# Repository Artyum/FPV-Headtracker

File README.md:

## FPH Headtracker for RC Airplanes

The FPH Headtracker is an advanced device designed for RC airplane enthusiasts. It enables pilots to control the camera on their RC aircraft by simply moving their head. This immersive technology enhances the flying experience by providing a first-person view (FPV) that moves naturally with the pilot's head movements. The headtracker system is equipped with sensors that accurately track the pilot's head position and transmit these movements to the camera gimbal on the RC airplane, allowing for precise and intuitive control. This innovation is particularly useful for aerial photography, racing, and immersive flight simulations, making the flying experience more engaging and realistic.

## Demonstration video
[MPX Mentor FPV with HEADTRACKER](https://www.youtube.com/watch?v=0JXXjhNscpw)

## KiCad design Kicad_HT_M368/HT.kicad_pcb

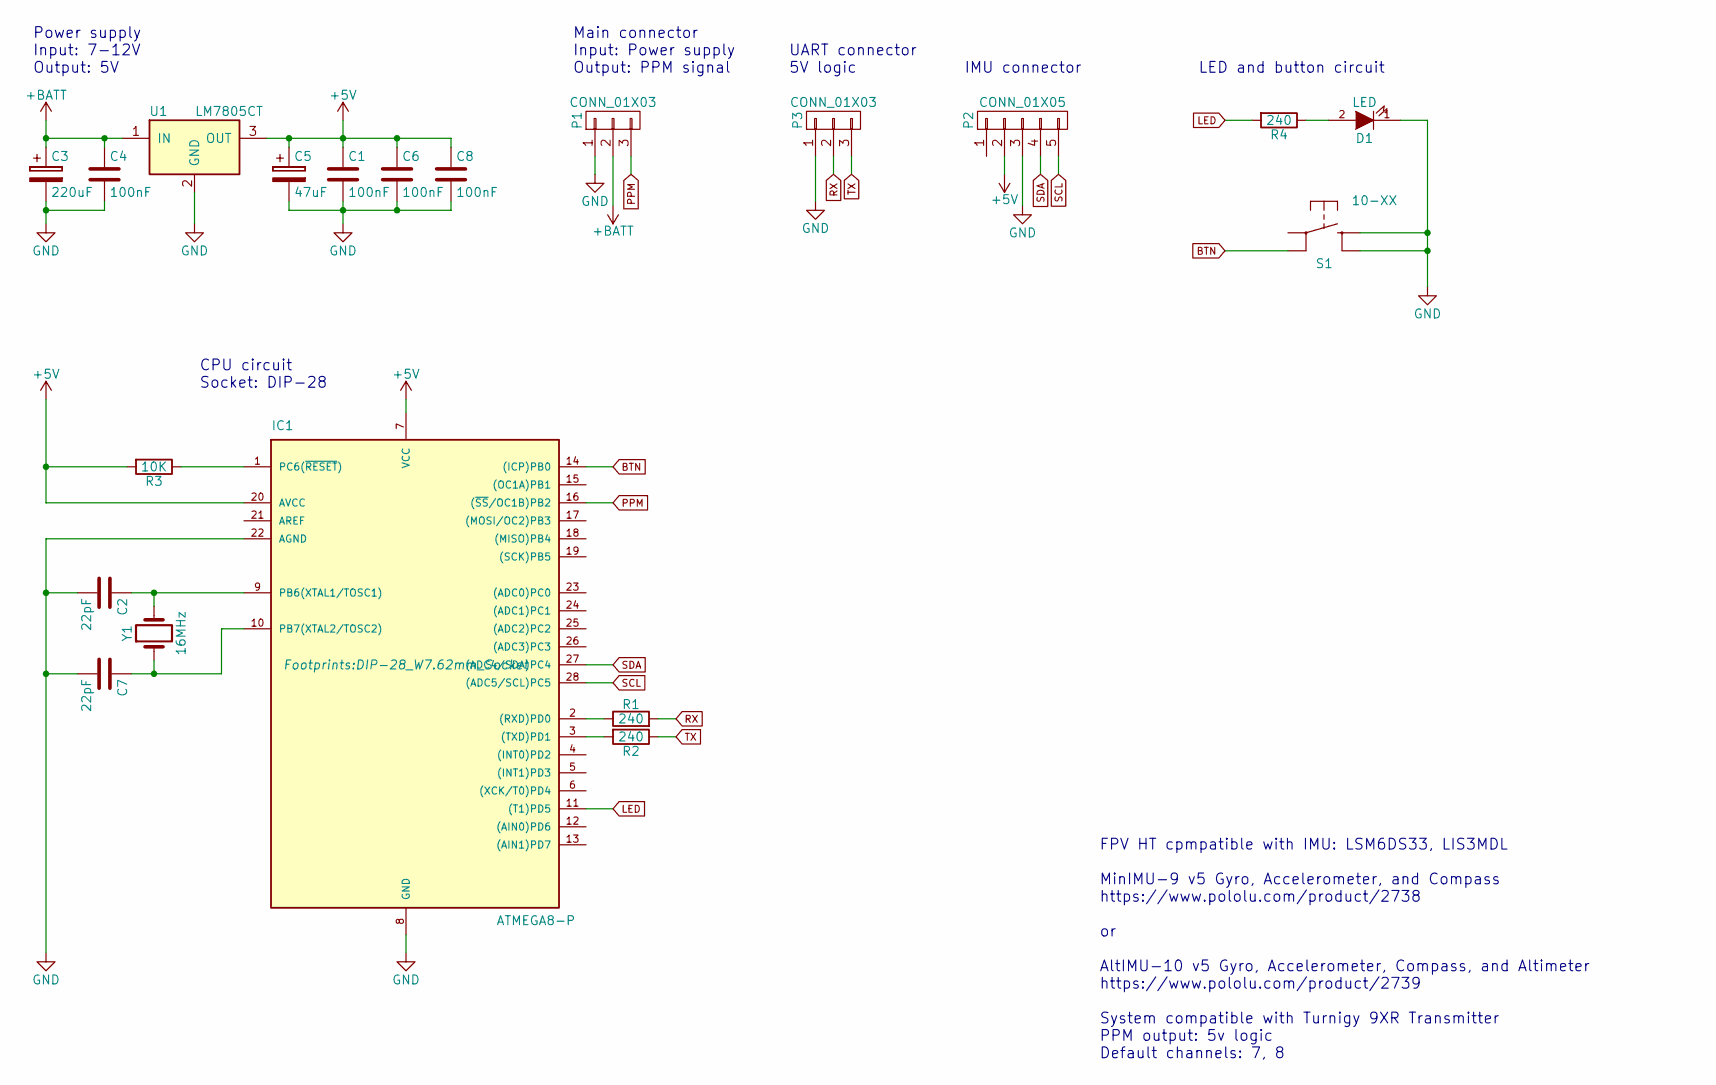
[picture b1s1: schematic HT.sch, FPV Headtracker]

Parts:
C1, C4, C6, C8: 100nF; C_Disc_D3_P2.5
C2, C7: 22pF; C_Disc_D3_P2.5
C3: 220uF; C_Radial_D5_L11_P2.5
C5: 47uF; C_Radial_D5_L11_P2.5
D1: LED; LED-3MM
IC1: ATMEGA8-P; DIP-28_W7.62mm_Socket
P1: CONN_01X03; Pin_Header_Angled_1x03
P2: CONN_01X05; Socket_Strip_Straight_1x05
P3: CONN_01X03; Pin_Header_Straight_1x03
R1, R2, R4: 240; R_Axial_DIN0207_L6.3mm_D2.5mm_P7.62mm_Horizontal
R3: 10K; R_Axial_DIN0207_L6.3mm_D2.5mm_P7.62mm_Horizontal
S1: 10-XX; B3F_10XX
U1: LM7805CT; TO-220_Horizontal
Y1: 16MHz; Crystal_HC49-4H_Vertical

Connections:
+5V: C1.1, C5.1, C6.1, C8.1, IC1.7 (VCC), IC1.20 (AVCC), P2.2, R3.2, U1.3 (OUT)
+BATT: C3.1, C4.1, P1.2, U1.1 (IN)
BTN: IC1.14 ((ICP)PB0), S1.4 (P1)
GND: C1.2, C2.2, C3.2, C4.2, C5.2, C6.2, C7.2, C8.2, D1.1 (K), IC1.8 (GND), IC1.22 (AGND), P1.1, P2.3, P3.1, S1.1 (S), S1.2 (S1), U1.2 (GND)
LED: IC1.11 ((T1)PD5), R4.2
unnamed: C2.1, IC1.9 (PB6(XTAL1/TOSC1)), Y1.2
unnamed: C7.1, IC1.10 (PB7(XTAL2/TOSC2)), Y1.1
unnamed: D1.2 (A), R4.1
unnamed: IC1.1 (PC6(~RESET~)), R3.1
unnamed: IC1.2 ((RXD)PD0), R1.1
unnamed: IC1.3 ((TXD)PD1), R2.2
PPM: IC1.16 ((~SS~/OC1B)PB2), P1.3
RX: P3.2, R1.2
SCL: IC1.28 ((ADC5/SCL)PC5), P2.5
SDA: IC1.27 ((ADC4/SDA)PC4), P2.4
TX: P3.3, R2.1

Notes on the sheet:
FPV HT cpmpatible with IMU: LSM6DS33, LIS3MDL MinIMU-9 v5 Gyro, Accelerometer, and Compass https://www.pololu.com/product/2738 or AltIMU-10 v5 Gyro, Accelerometer, Compass, and Altimeter https://www.pololu.com/product/2739 System compatible with Turnigy 9XR Transmitter PPM output: 5v logic Default 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
Power supply Input: 7-12V Output: 5V
Main connector Input: Power supply Output: PPM signal
UART connector 5V logic
IMU connector
LED and button circuit
CPU circuit Socket: DIP-28

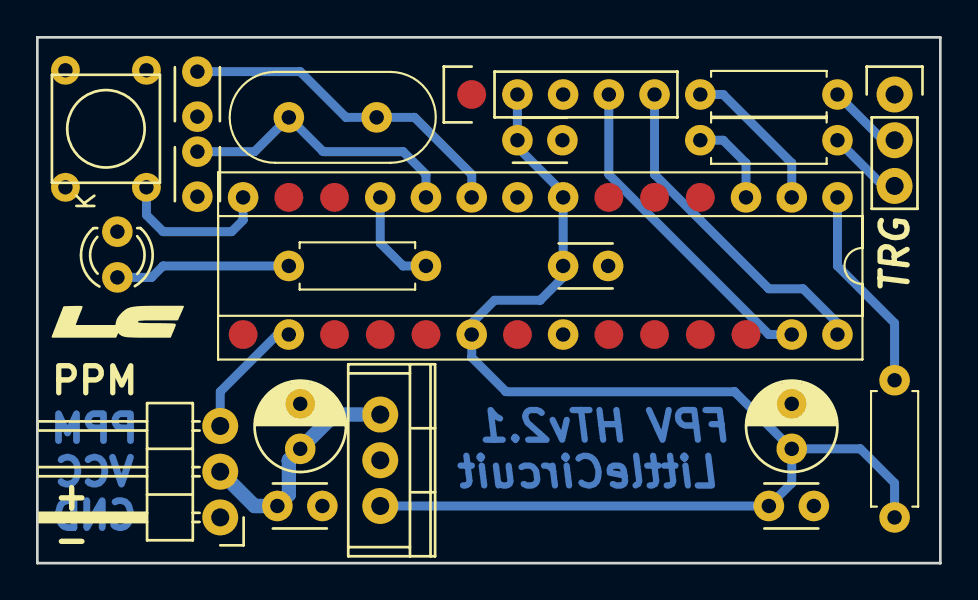
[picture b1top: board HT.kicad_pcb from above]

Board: 2 copper layers, 50.2 x 29.2 mm, 20 parts (0 on the bottom side), 16 nets.

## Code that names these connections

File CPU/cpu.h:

#ifndef CPU_CPU_H_
#define CPU_CPU_H_

#include <avr/io.h>
#include <avr/interrupt.h>

#include "../FUNC/func.h"
#include "../BTN/btn.h"
#include "../UART/uart.h"

//PPM OUT
#define PPM_DDR DDRB
#define PPM_PORT PORTB
#define PPM_PIN PB2

//LED
#define LED_DDR DDRD
#define LED_PORT PORTD
#define LED_PIN PD5

//Button
#define BTN_DDR DDRB
#define BTN_PORT PORTB
#define BTN_PINPORT PINB
#define BTN_PIN PB0

/////////////////////////////////////////////////////////////////////////////////////////////////
//Macros
#define PIN_LOW(PORT,PIN) PORT &= ~(1<<PIN)
#define PIN_HIGH(PORT,PIN) PORT |= (1<<PIN)
#define PIN_TOG(PORT,PIN) PORT ^= (1<<PIN)

#define LED_ON PIN_HIGH(LED_PORT,LED_PIN)
#define LED_OFF PIN_LOW(LED_PORT,LED_PIN)
#define LED_TOG PIN_TOG(LED_PORT,LED_PIN)

#define READ_PIN(PINPORT,PIN) (PINPORT & (1<<PIN))

extern volatile uint16_t t_resetpos;
extern volatile uint16_t t_ms;

void cpu_init(void);

#endif /* CPU_CPU_H_ */

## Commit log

2024-07-26 Init
2024-07-26 Create LICENSE
